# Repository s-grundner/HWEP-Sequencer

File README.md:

# HWEP - Sequencer [DE]

|           Neueste Renderung der Platine         |            Assemblierter Prototyp               |
|:-----------------------------------------------:|:-----------------------------------------------:|
|||

## Projektstatus

MIDI Erweiterung in Arbeit. CAD dateien e.g. Gehäuse sind noch nicht im Projekt inkludiert.
Um die Diagramme in der Dokumentation gut erkennen zu können, empfiehlt sich, das Dark-Mode-Theme von GitHub zu Verwenden.

## Repository Struktur

 - [**Hardware DOCS**](manufacturing/hwep_sequencer_v2)
 - [**Software DOCS**](src/SRC_HWEP_Sequencer_V2)

## KUB - Kurzbeschreibung

Der Sequenzer ist ein musisches Instrument, welches vom Benutzer einstellbare Töne nacheinander abspielt und dadurch eine Melodie erzeugt. Die Tonlage wird durch Potentiometer analog eingestellt und anschließend an die chromatische Skala angepasst. Die acht Töne werden mit jeder steigenden Flanke des Takts durchgeschaltet.

Mit einem Pause-Taster kann der Zyklus pausiert werden. Mit dem Reset-Taster kann zum Anfang des Zyklus gesprungen werden. Der "Show Key" Taster zeigt bei Betätigung die Gespielten Noten am Display an. Der Sequencer ist mit zwei Prescalern für Gate-Länge und Taktrate ausgestattet. Dieser teilt den Takt oder das Gate des Tones durch 1, 2, 4, 8 oder 16. Außerdem verfügt der Sequencer über eine Umschalttaste (Shift), die das Funktionsspektrum erweitern. Die Dokumentation für die Taster befindet sich in der Funktionsbeschreibung.

Zum Bedienen des Sequencers gibt es verschiedene Parameter, die mithilfe eines Dreh-Encoders gesteuert werden können. Der Dreh-Encoder hat einen integrierten Taster, mit welchem man die Parameter, die man verändern will, einstellen kann. Die Veränderung der Parameter wird je nach Modus an verschiedenen Status LEDs und Anzeigen abgezeichnet.

Der Sequencer wird mit dem einem RTOS am ESP32 32-bit Microcontroller betrieben. Der Digitale Audioausgang erfolgt über das I²S (Inter-IC-Sound) Protokoll und kann 16-Bit Sounds bei einer Abtastrate von 44.1kHz übertragen und durch einen I²S-DAC (PCM5102a) direkt als Audio-Signal ausgegeben werden.

## FUB - Funktionsbeschreibung

#### 1. 8 Potentiometer als analoger Eingang

 - dient als analoger Eingang für die Tonlage der einzelnen Töne
 - jedes Potentiometer umfasst 24 Halbtöne bzw. zwei Oktaven
 - die analogen Werte einem 8 Channel ADC (ADC088S052) über die SPI Schnittstelle eingelesen

#### 2. 16 Status LED’s:

 - 8 EN-LED’s:
   - zeigen an, welcher Ton spielen wird oder stummgeschalten ist (LED aus)
 - 8 Index/Cursor-LED’s:
   - **Index:** zeigen an, welcher Ton gerade spielt
   - **Cursor:** dient zum Anzeigen eines Cursors

#### 3. 3x 7-Segent Display:

 - nützen zur Anzeige von Parametern
 - werden mit einem MCP23S08 via die SPI Schnittstelle seriell angesteuert
 
#### 4. Dreh-Encoder:

 - zum Einstellen der Parameter der verschiedenen Modi
 - um den Drehencoder befinden sich 12 RGB-LED’s, welche den Rotationstatus anzeigen
 
#### 5. Taster: 

> Jeder Taster wird mittels eines MCP23S08 via SPI eingelesen.

 - **Pause:** pausiert den Zyklus
 - **Reset:** setzt den Zyklus asynchron zurück
 - **Show Keys:** zeigt die gespielten Noten am Display
 - **Shift:** zum Einstellen der Parameter der verschiedenen Modi
 - e. **Prescaler:** einstellen von zwei verschiedenen Prescalern für Gate und Takt
   - 5 Taster für jeden Prescaler
   - Tasten werden auf 4-Bit Priorität-Encodiert
 
#### 6. 4 Modi

> Jeder Modus verändert die Anzeigen an den Status LED’s und Displays bzw. die Funktionalität verschiedener Eingaben. Nach wechseln eines Modus wird der aktuelle Modus am 7-Segment Display angezeigt, bis die Anzeige benötigt wird, um einen Parameter anzuzeigen.
 
 - BPM:
   - **7-Segment Display:** zeigt die eingestellten BPM bzw. die Wellenform an
   - **Index/Cursor:** zeigt den Index an
   - **Drehencoder:** zum Verändern der BPM
   - **Shift Taster:** Drehencoder verändert die Wellenform
 - Tonleiter Einstellungen:
   - **7-Segment Display:** zeigt den Tonleiter bzw. den Modalen Tonleiter an.
   - **Index/Cursor:** zeigt den Index an
   - **Drehencoder:** zum Verändern den Tonleiter
   - **Shift Taster:** verändert den Modus des Tonleiters (Dur,Moll…)
 - Enable/Reset:
   - **7-Segment Display:**
   - **Index/Cursor:** zeigt den Cursor an
   - **Drehencoder:** bewegt den Cursor. Dort wo der Cursor stehen bleibt, setzt sich der Zyklus zurück.
   - **Shift Taster:** stummt/entstummt einen Ton an der Cursorstellung
 
 - Transpose:
   - **7-Segment Display:** zeigt an um wieviel Halbtöne die Melodie transponiert wird
   - **Index/Cursor:** zeigt den Index an
   - **Drehencoder:** Transponiert die Tonlage um einen Halbton
   - **Shift Taster:** Drehencoder verändert die Tonlage um eine Oktave
 
#### 7. ESP32 32-Bit Microcontroller:

 - Zentrale Recheneinheit für den Sequenzer
 - Berechnung der Wavetables
 - SPI als Übertragungsprotokoll zur Ansteuerung der internen Peripherien
 - Audio-Output:
   - Digitale Audioübertragung via I²S Protokoll
   - 16-bit Audio-Signale mit Abtastrate von 44,1kHz
   - Ein I²S-DAC (PCM5102a) decodiert die Audio-Daten und gibt sie Analog an eine 3,5mm Klinkenbuchse aus.
   - Kompatibel mit Trinity Endstufe

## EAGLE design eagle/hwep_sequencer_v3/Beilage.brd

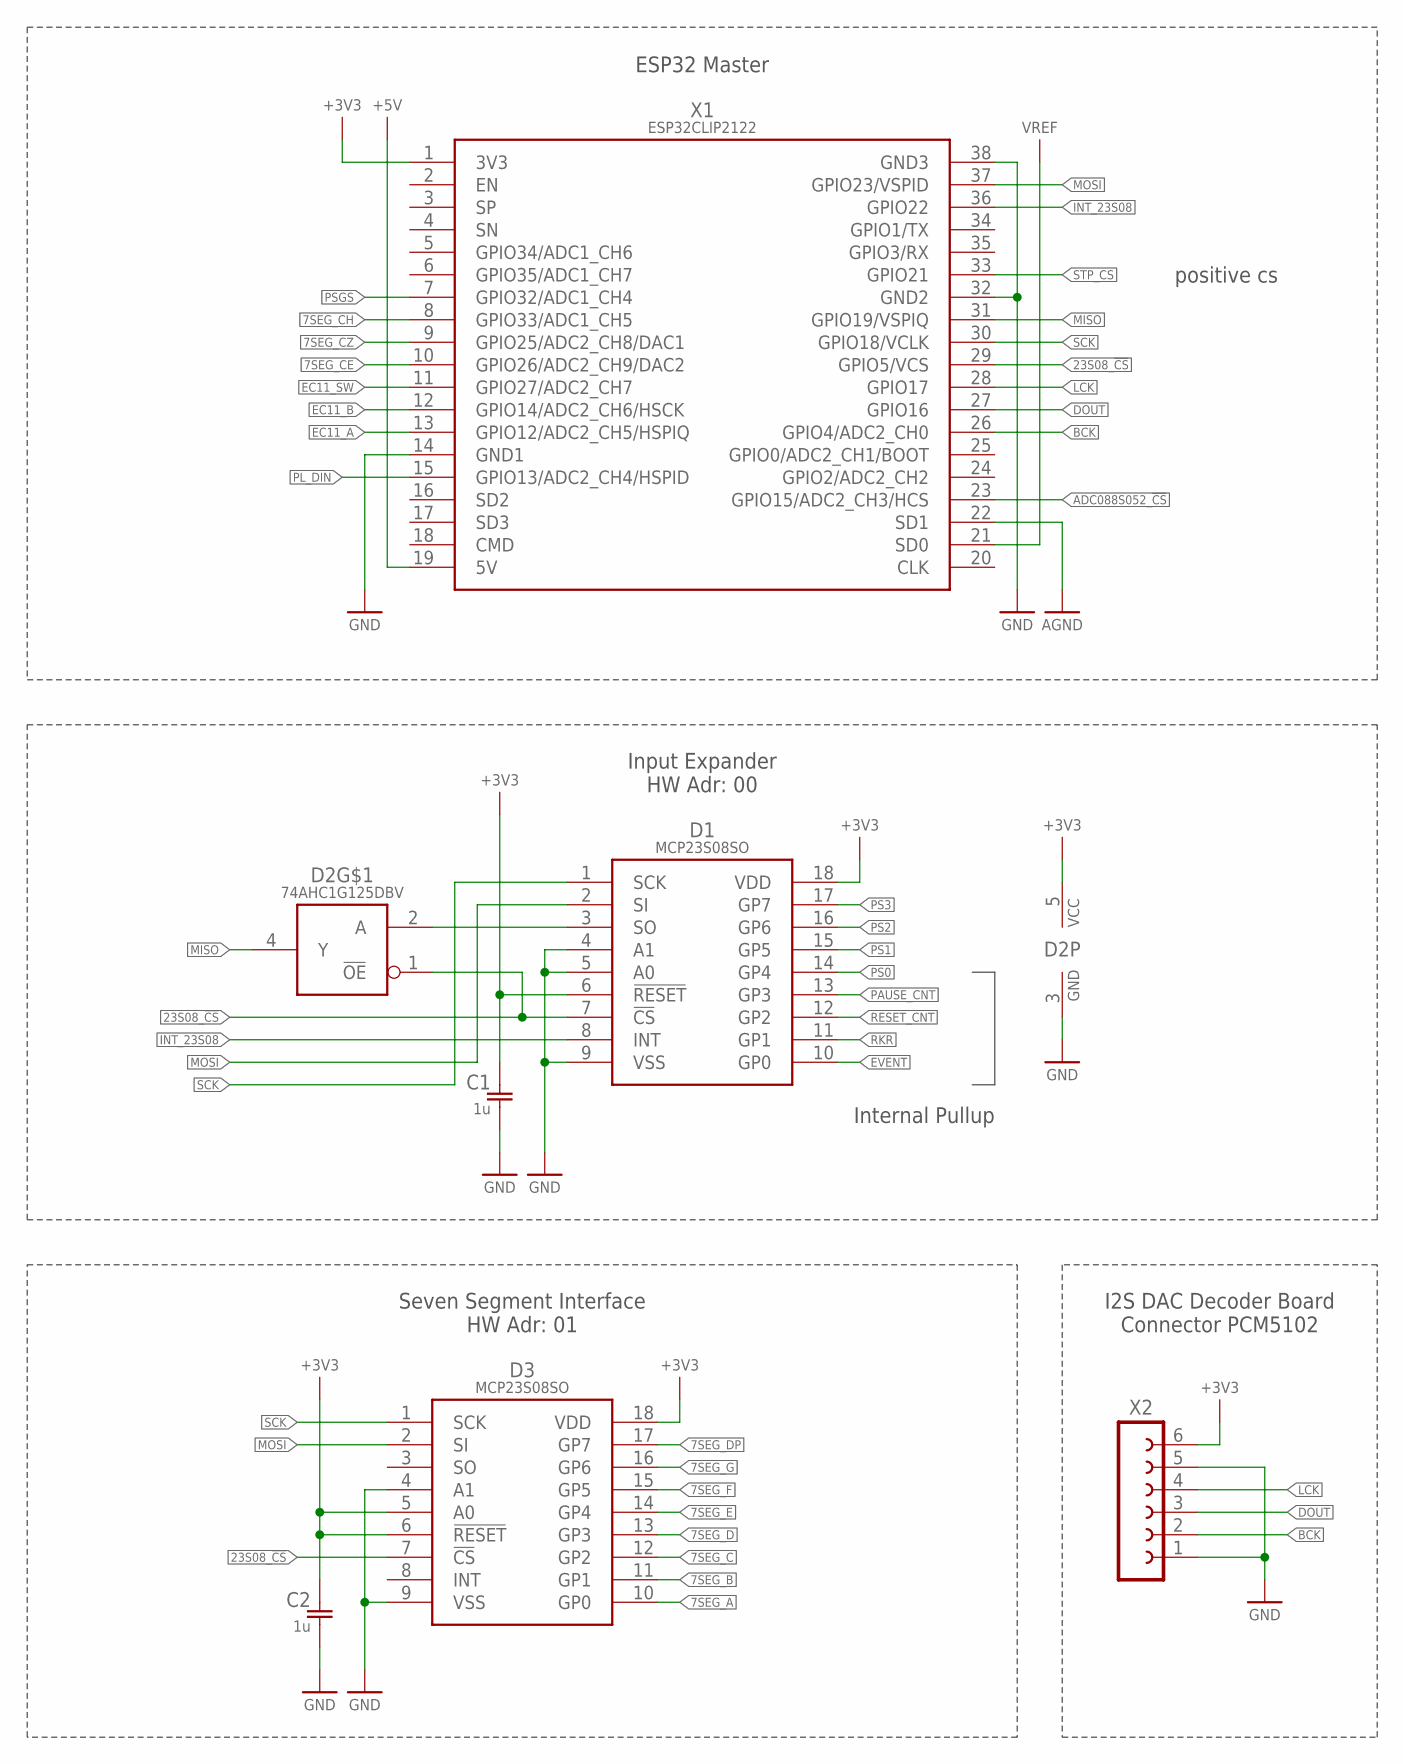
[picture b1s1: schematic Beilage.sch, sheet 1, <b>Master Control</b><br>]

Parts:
C1, C2: 1u; C0805
D1, D3: MCP23S08SO; SO18W
D2: 74AHC1G125DBV; SOT23-5
X1: ESP32CLIP2122; ESP32-DEVKIT-C-CLIP
X2: FE06-1; FE06

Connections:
7SEG_A: D3.10 (GP0); also elsewhere on the board
7SEG_B: D3.11 (GP1); also elsewhere on the board
7SEG_C: D3.12 (GP2); also elsewhere on the board
7SEG_CE: X1.10 (GPIO26/ADC2_CH9/DAC2); also elsewhere on the board
7SEG_CH: X1.8 (GPIO33/ADC1_CH5); also elsewhere on the board
7SEG_CZ: X1.9 (GPIO25/ADC2_CH8/DAC1); also elsewhere on the board
7SEG_D: D3.13 (GP3); also elsewhere on the board
7SEG_DP: D3.17 (GP7); also elsewhere on the board
7SEG_E: D3.14 (GP4); also elsewhere on the board
7SEG_F: D3.15 (GP5); also elsewhere on the board
7SEG_G: D3.16 (GP6); also elsewhere on the board
23S08_!CS: D1.7 (!CS), D2.1 (!OE), D3.7 (!CS), X1.29 (GPIO5/VCS)
+3V3: C1.1, C2.1, D1.6 (!RESET), D1.18 (VDD), D2.5 (VCC), D3.5 (A0), D3.6 (!RESET), D3.18 (VDD), X1.1 (3V3), X2.6; also elsewhere on the board
+5V: X1.19 (5V); also elsewhere on the board
ADC088S052_!CS: X1.23 (GPIO15/ADC2_CH3/HCS); also elsewhere on the board
AGND: X1.22 (SD1); also elsewhere on the board
BCK: X1.26 (GPIO4/ADC2_CH0), X2.2
DOUT: X1.27 (GPIO16), X2.3
EC11_A: X1.13 (GPIO12/ADC2_CH5/HSPIQ); also elsewhere on the board
EC11_B: X1.12 (GPIO14/ADC2_CH6/HSCK); also elsewhere on the board
EC11_SW: X1.11 (GPIO27/ADC2_CH7); also elsewhere on the board
EVENT: D1.10 (GP0); also elsewhere on the board
GND: C1.2, C2.2, D1.4 (A1), D1.5 (A0), D1.9 (VSS), D2.3 (GND), D3.4 (A1), D3.9 (VSS), X1.14 (GND1), X1.32 (GND2), X1.38 (GND3), X2.1, X2.5; also elsewhere on the board
INT_23S08: D1.8 (INT), X1.36 (GPIO22)
LCK: X1.28 (GPIO17), X2.4
MISO: D2.4 (Y), X1.31 (GPIO19/VSPIQ); also elsewhere on the board
MOSI: D1.2 (SI), D3.2 (SI), X1.37 (GPIO23/VSPID); also elsewhere on the board
unnamed: D1.3 (SO), D2.2 (A)
PAUSE_CNT: D1.13 (GP3); also elsewhere on the board
PL_DIN: X1.15 (GPIO13/ADC2_CH4/HSPID); also elsewhere on the board
PS0: D1.14 (GP4); also elsewhere on the board
PS1: D1.15 (GP5); also elsewhere on the board
PS2: D1.16 (GP6); also elsewhere on the board
PS3: D1.17 (GP7); also elsewhere on the board
PSGS: X1.7 (GPIO32/ADC1_CH4); also elsewhere on the board
RESET_CNT: D1.12 (GP2); also elsewhere on the board
RKR: D1.11 (GP1); also elsewhere on the board
SCK: D1.1 (SCK), D3.1 (SCK), X1.30 (GPIO18/VCLK); also elsewhere on the board
STP_CS: X1.33 (GPIO21); also elsewhere on the board
VREF: X1.21 (SD0); also elsewhere on the board

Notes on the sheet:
Seven Segment Interface HW Adr: 01
ESP32 Master
I2S DAC Decoder Board Connector PCM5102
Input Expander HW Adr: 00
Internal Pullup
positive cs

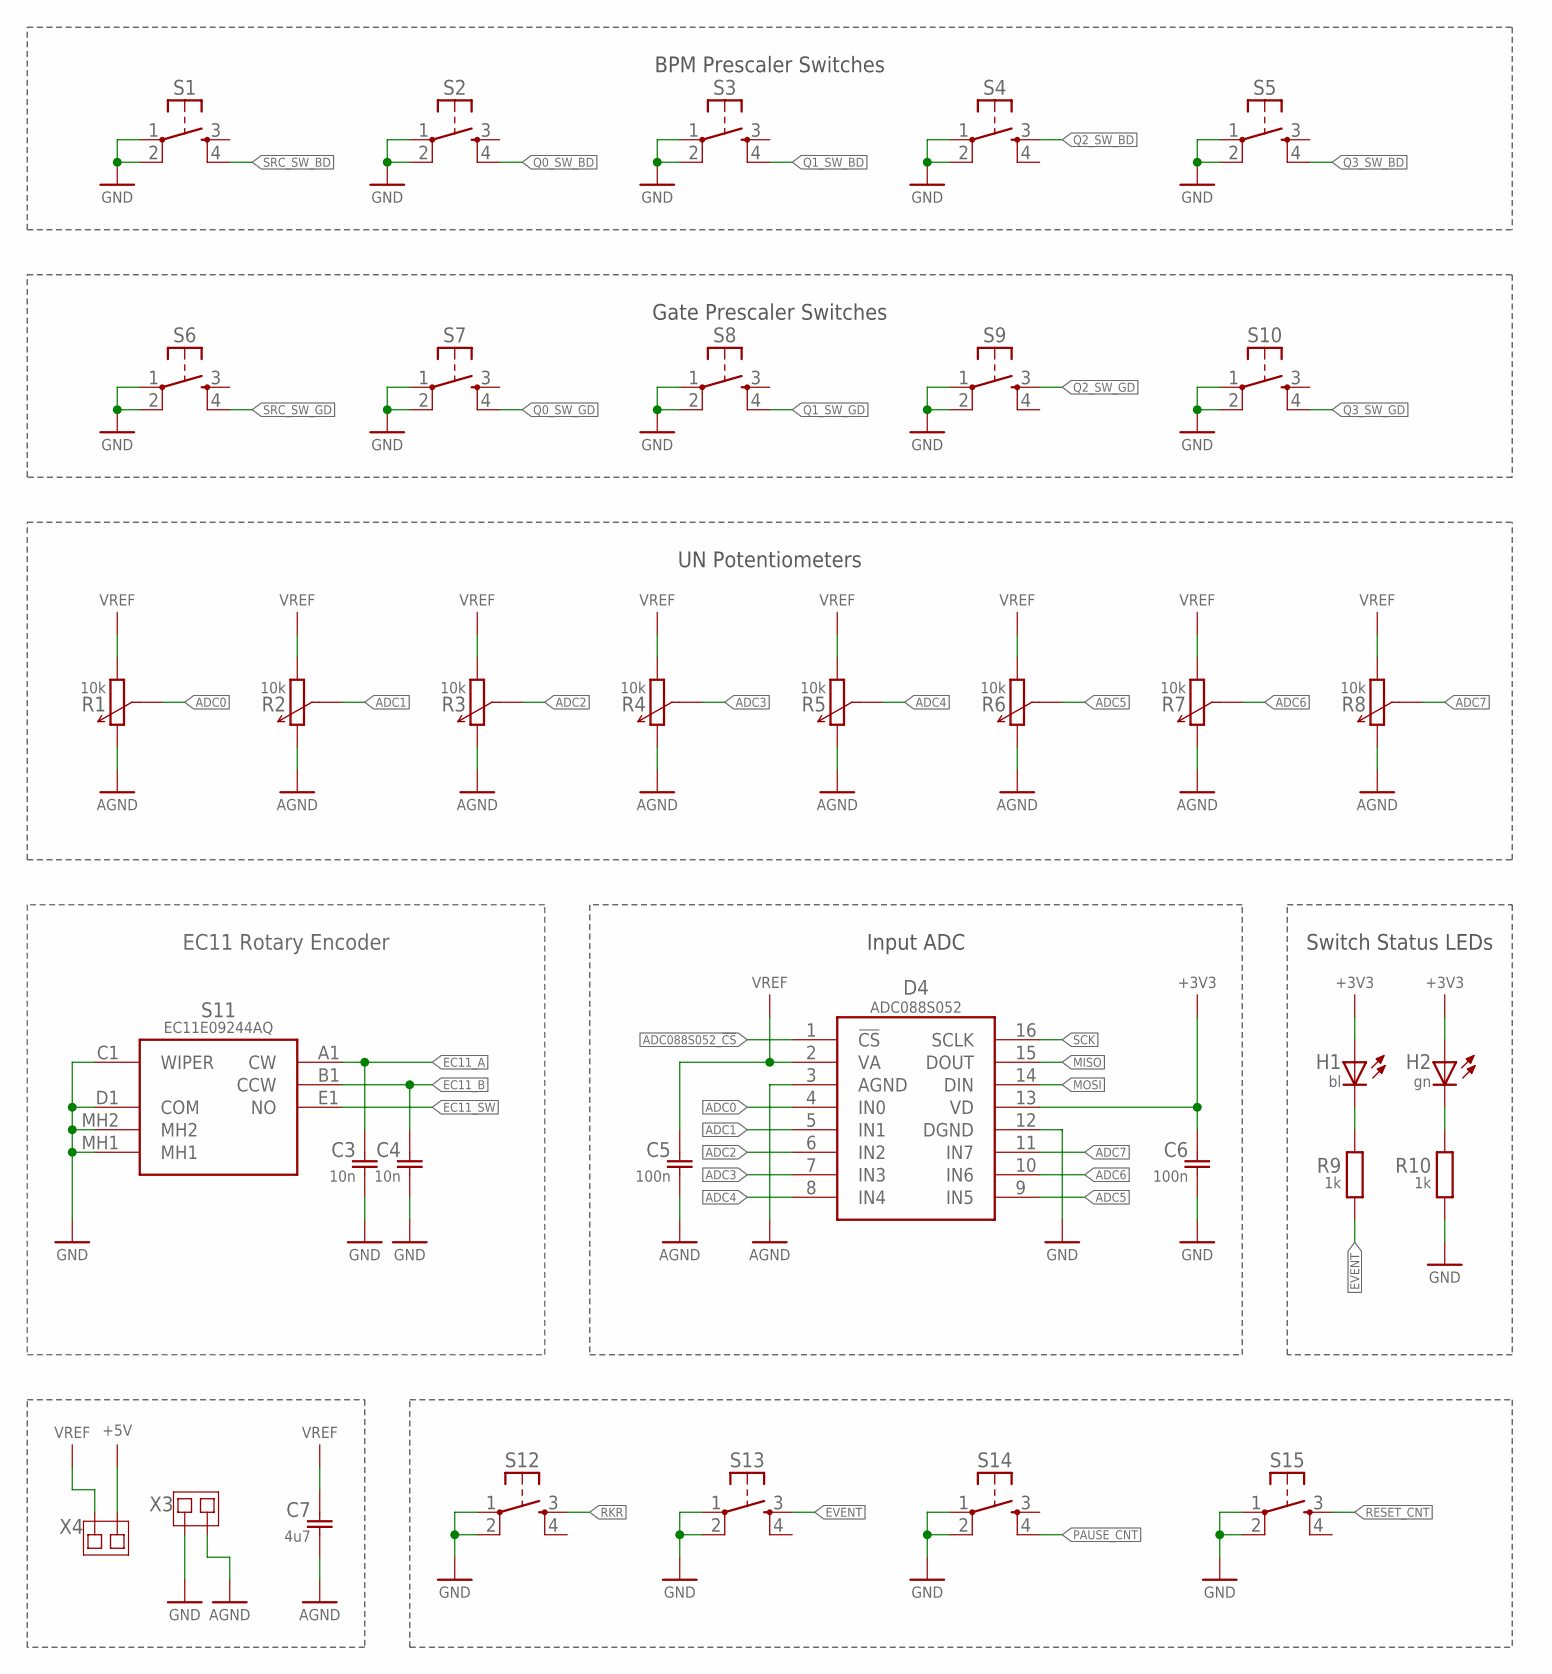
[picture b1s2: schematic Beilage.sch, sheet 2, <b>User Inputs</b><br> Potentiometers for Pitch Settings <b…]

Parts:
C3, C4: 10n; C0805
C5, C6: 100n; C0805
C7: 4u7; C0805
D4: ADC088S052; TSSOP16
H1: bl; CHIPLED_1206
H2: gn; CHIPLED_1206
R1, R2, R3, R4, R5, R6, R7, R8: 10k; P160LB
R9, R10: 1k; R0805
S1, S2, S3, S4, S5, S6, S7, S8, S9, S10, S12, S13, S14, S15: TASTE10XX; B3F-10XX
S11: EC11E09244AQ; EC11
X3, X4: JUMPSMD1FACH-1; MYLIB_SJ

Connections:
+3V3: C6.1, D4.13 (VD), H1.A, H2.A; also elsewhere on the board
+5V: X4.1; also elsewhere on the board
ADC0: D4.4 (IN0), R1.2 (3)
ADC1: D4.5 (IN1), R2.2 (3)
ADC2: D4.6 (IN2), R3.2 (3)
ADC3: D4.7 (IN3), R4.2 (3)
ADC4: D4.8 (IN4), R5.2 (3)
ADC5: D4.9 (IN5), R6.2 (3)
ADC6: D4.10 (IN6), R7.2 (3)
ADC7: D4.11 (IN7), R8.2 (3)
ADC088S052_!CS: D4.1 (!CS); also elsewhere on the board
AGND: C5.2, C7.2, D4.3 (AGND), R1.3 (2), R2.3 (2), R3.3 (2), R4.3 (2), R5.3 (2), R6.3 (2), R7.3 (2), R8.3 (2), X3.2; also elsewhere on the board
EC11_A: C3.1, S11.A1 (CW); also elsewhere on the board
EC11_B: C4.1, S11.B1 (CCW); also elsewhere on the board
EC11_SW: S11.E1 (NO); also elsewhere on the board
EVENT: R9.1, S13.3 (S); also elsewhere on the board
GND: C3.2, C4.2, C6.2, D4.12 (DGND), R10.1, S1.1, S1.2 (P1), S2.1, S2.2 (P1), S3.1, S3.2 (P1), S4.1, S4.2 (P1), S5.1, S5.2 (P1), S6.1, S6.2 (P1), S7.1, S7.2 (P1), S8.1, S8.2 (P1), S9.1, S9.2 (P1), S10.1, S10.2 (P1), S11.C1 (WIPER), S11.D1 (COM), S11.MH1, S11.MH2, S12.1, S12.2 (P1), S13.1, S13.2 (P1), S14.1, S14.2 (P1), S15.1, S15.2 (P1), X3.1; also elsewhere on the board
MISO: D4.15 (DOUT); also elsewhere on the board
MOSI: D4.14 (DIN); also elsewhere on the board
unnamed: H2.C, R10.2
unnamed: H1.C, R9.2
PAUSE_CNT: S14.4 (S1); also elsewhere on the board
Q0_SW_BD: S2.4 (S1); also elsewhere on the board
Q0_SW_GD: S7.4 (S1); also elsewhere on the board
Q1_SW_BD: S3.4 (S1); also elsewhere on the board
Q1_SW_GD: S8.4 (S1); also elsewhere on the board
Q2_SW_BD: S4.3 (S); also elsewhere on the board
Q2_SW_GD: S9.3 (S); also elsewhere on the board
Q3_SW_BD: S5.4 (S1); also elsewhere on the board
Q3_SW_GD: S10.4 (S1); also elsewhere on the board
RESET_CNT: S15.3 (S); also elsewhere on the board
RKR: S12.3 (S); also elsewhere on the board
SCK: D4.16 (SCLK); also elsewhere on the board
SRC_SW_BD: S1.4 (S1); also elsewhere on the board
SRC_SW_GD: S6.4 (S1); also elsewhere on the board
VREF: C5.1, C7.1, D4.2 (VA), R1.1, R2.1, R3.1, R4.1, R5.1, R6.1, R7.1, R8.1, X4.2; also elsewhere on the board

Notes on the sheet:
UN Potentiometers
EC11 Rotary Encoder
BPM Prescaler Switches
Gate Prescaler Switches
Switch Status LEDs
Input ADC

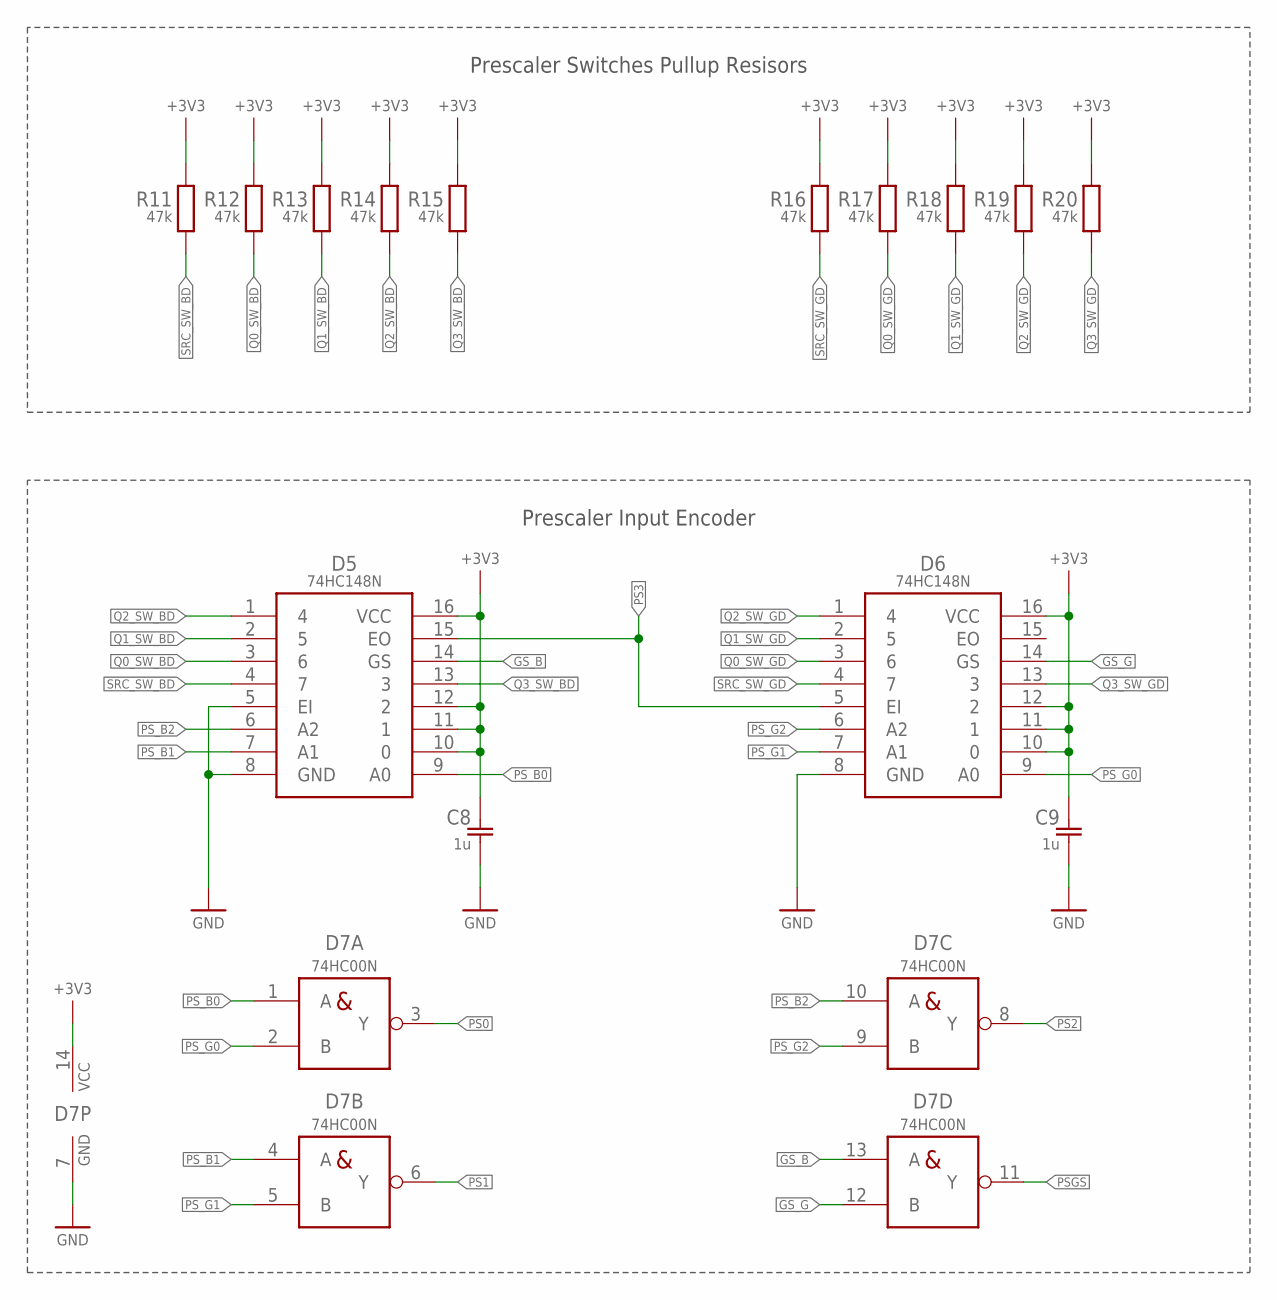
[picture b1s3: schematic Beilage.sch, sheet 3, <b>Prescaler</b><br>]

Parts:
C8, C9: 1u; C0805
D5, D6: 74HC148N; DIP16
D7: 74HC00N; DIP14
R11, R12, R13, R14, R15, R16, R17, R18, R19, R20: 47k; R0805

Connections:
+3V3: C8.1, C9.1, D5.10 (0), D5.11 (1), D5.12 (2), D5.16 (VCC), D6.10 (0), D6.11 (1), D6.12 (2), D6.16 (VCC), D7.14 (VCC), R11.2, R12.2, R13.2, R14.2, R15.2, R16.2, R17.2, R18.2, R19.2, R20.2; also elsewhere on the board
GND: C8.2, C9.2, D5.5 (EI), D5.8 (GND), D6.8 (GND), D7.7 (GND); also elsewhere on the board
GS_B: D5.14 (GS), D7.13 (A)
GS_G: D6.14 (GS), D7.12 (B)
PS0: D7.3 (Y); also elsewhere on the board
PS1: D7.6 (Y); also elsewhere on the board
PS2: D7.8 (Y); also elsewhere on the board
PS3: D5.15 (EO), D6.5 (EI); also elsewhere on the board
PSGS: D7.11 (Y); also elsewhere on the board
PS_B0: D5.9 (A0), D7.1 (A)
PS_B1: D5.7 (A1), D7.4 (A)
PS_B2: D5.6 (A2), D7.10 (A)
PS_G0: D6.9 (A0), D7.2 (B)
PS_G1: D6.7 (A1), D7.5 (B)
PS_G2: D6.6 (A2), D7.9 (B)
Q0_SW_BD: D5.3 (6), R12.1; also elsewhere on the board
Q0_SW_GD: D6.3 (6), R17.1; also elsewhere on the board
Q1_SW_BD: D5.2 (5), R13.1; also elsewhere on the board
Q1_SW_GD: D6.2 (5), R18.1; also elsewhere on the board
Q2_SW_BD: D5.1 (4), R14.1; also elsewhere on the board
Q2_SW_GD: D6.1 (4), R19.1; also elsewhere on the board
Q3_SW_BD: D5.13 (3), R15.1; also elsewhere on the board
Q3_SW_GD: D6.13 (3), R20.1; also elsewhere on the board
SRC_SW_BD: D5.4 (7), R11.1; also elsewhere on the board
SRC_SW_GD: D6.4 (7), R16.1; also elsewhere on the board

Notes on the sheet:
Prescaler Input Encoder
Prescaler Switches Pullup Resisors

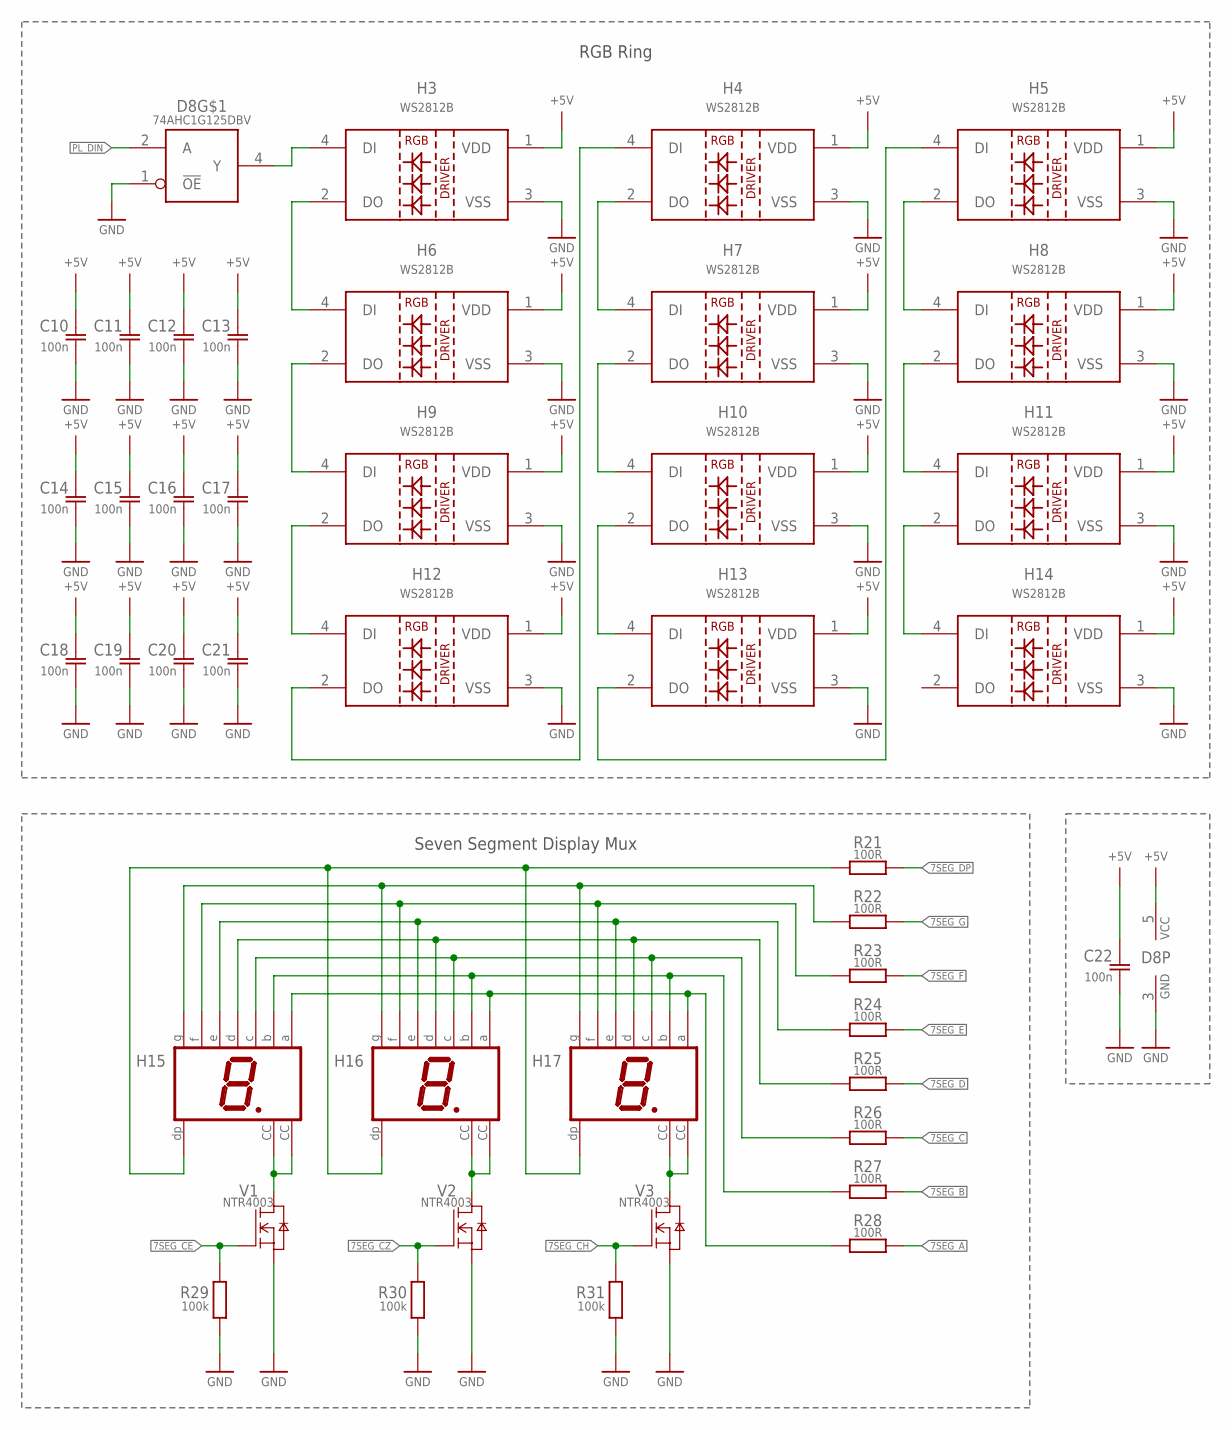
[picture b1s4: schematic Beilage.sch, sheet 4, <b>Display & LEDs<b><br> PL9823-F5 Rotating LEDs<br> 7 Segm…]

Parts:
C10, C11, C12, C13, C14, C15, C16, C17, C18, C19, C20, C21, C22: 100n; C0805
D8: 74AHC1G125DBV; SOT23-5
H3, H4, H5, H6, H7, H8, H9, H10, H11, H12, H13, H14: WS2812B
H15, H16, H17: HD-H103; HDSP-E
R21, R22, R23, R24, R25, R26, R27, R28: 100R; R0805
R29, R30, R31: 100k; R0805
V1, V2, V3: NTR4003; SOT23

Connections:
7SEG_A: R28.2; also elsewhere on the board
7SEG_B: R27.2; also elsewhere on the board
7SEG_C: R26.2; also elsewhere on the board
7SEG_CE: R29.2, V1.1 (G); also elsewhere on the board
7SEG_CH: R31.2, V3.1 (G); also elsewhere on the board
7SEG_CZ: R30.2, V2.1 (G); also elsewhere on the board
7SEG_D: R25.2; also elsewhere on the board
7SEG_DP: R21.2; also elsewhere on the board
7SEG_E: R24.2; also elsewhere on the board
7SEG_F: R23.2; also elsewhere on the board
7SEG_G: R22.2; also elsewhere on the board
+5V: C10.1, C11.1, C12.1, C13.1, C14.1, C15.1, C16.1, C17.1, C18.1, C19.1, C20.1, C21.1, C22.1, D8.5 (VCC), H3.1 (VDD), H4.1 (VDD), H5.1 (VDD), H6.1 (VDD), H7.1 (VDD), H8.1 (VDD), H9.1 (VDD), H10.1 (VDD), H11.1 (VDD), H12.1 (VDD), H13.1 (VDD), H14.1 (VDD); also elsewhere on the board
GND: C10.2, C11.2, C12.2, C13.2, C14.2, C15.2, C16.2, C17.2, C18.2, C19.2, C20.2, C21.2, C22.2, D8.1 (!OE), D8.3 (GND), H3.3 (VSS), H4.3 (VSS), H5.3 (VSS), H6.3 (VSS), H7.3 (VSS), H8.3 (VSS), H9.3 (VSS), H10.3 (VSS), H11.3 (VSS), H12.3 (VSS), H13.3 (VSS), H14.3 (VSS), R29.1, R30.1, R31.1, V1.2 (S), V2.2 (S), V3.2 (S); also elsewhere on the board
unnamed: D8.4 (Y), H3.4 (DI)
unnamed: H6.2 (DO), H9.4 (DI)
unnamed: H3.2 (DO), H6.4 (DI)
unnamed: H8.2 (DO), H11.4 (DI)
unnamed: H15.DP, H16.DP, H17.DP, R21.1
unnamed: H15.G, H16.G, H17.G, R22.1
unnamed: H15.F, H16.F, H17.F, R23.1
unnamed: H15.A, H16.A, H17.A, R28.1
unnamed: H15.B, H16.B, H17.B, R27.1
unnamed: H15.CC1 (CC), H15.CC2 (CC), V1.3 (D)
unnamed: H15.D, H16.D, H17.D, R25.1
unnamed: H10.2 (DO), H13.4 (DI)
unnamed: H5.4 (DI), H13.2 (DO)
unnamed: H5.2 (DO), H8.4 (DI)
unnamed: H16.CC1 (CC), H16.CC2 (CC), V2.3 (D)
unnamed: H17.CC1 (CC), H17.CC2 (CC), V3.3 (D)
unnamed: H7.2 (DO), H10.4 (DI)
unnamed: H9.2 (DO), H12.4 (DI)
unnamed: H11.2 (DO), H14.4 (DI)
unnamed: H4.4 (DI), H12.2 (DO)
unnamed: H4.2 (DO), H7.4 (DI)
unnamed: H15.C, H16.C, H17.C, R26.1
unnamed: H15.E, H16.E, H17.E, R24.1
PL_DIN: D8.2 (A); also elsewhere on the board

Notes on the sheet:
Seven Segment Display Mux
RGB Ring

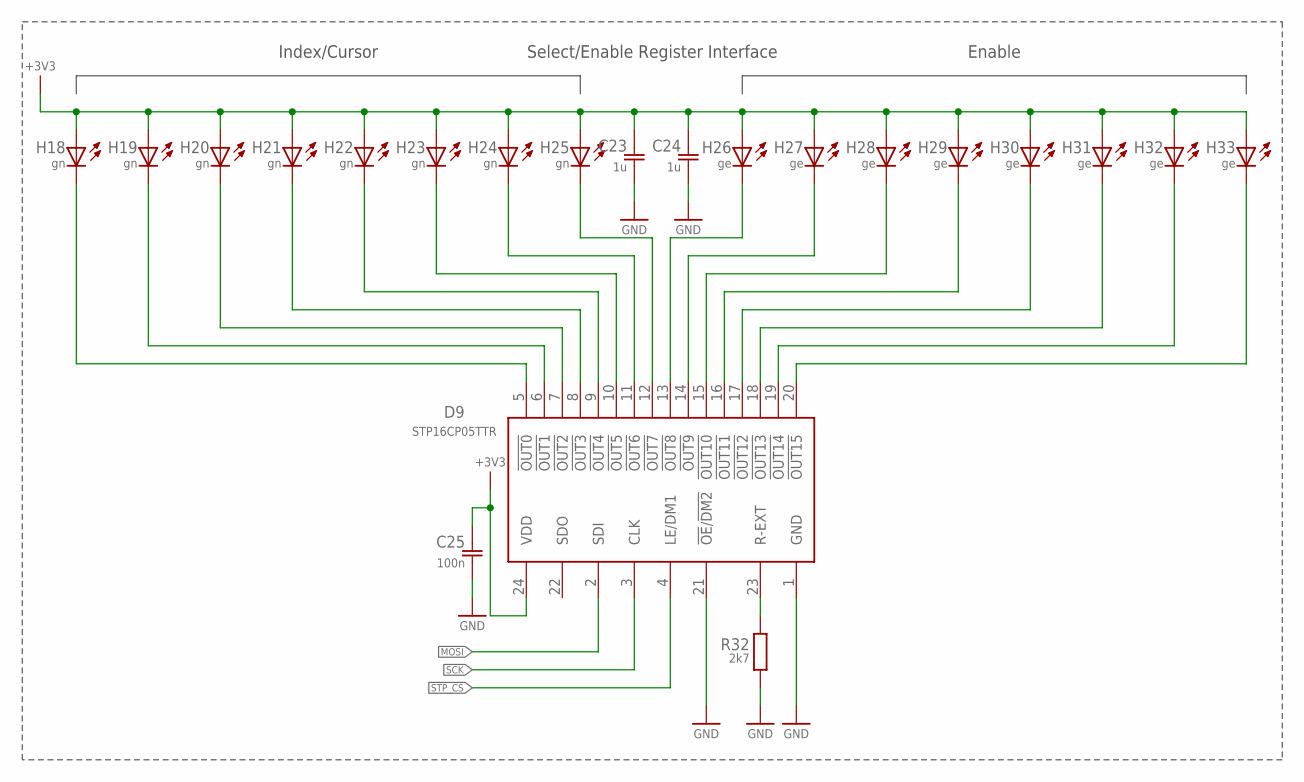
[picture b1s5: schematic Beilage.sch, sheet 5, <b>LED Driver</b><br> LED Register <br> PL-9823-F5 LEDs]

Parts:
C23, C24: 1u; C0805
C25: 100n; C0805
D9: STP16CP05TTR; TSSOP24
H18, H19, H20, H21, H22, H23, H24, H25: gn; LED5MM
H26, H27, H28, H29, H30, H31, H32, H33: ge; LED5MM
R32: 2k7; R0805

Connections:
+3V3: C23.1, C24.1, C25.1, D9.24 (VDD), H18.A, H19.A, H20.A, H21.A, H22.A, H23.A, H24.A, H25.A, H26.A, H27.A, H28.A, H29.A, H30.A, H31.A, H32.A, H33.A; also elsewhere on the board
GND: C23.2, C24.2, C25.2, D9.1 (GND), D9.21 (!OE!/!DM2), R32.1; also elsewhere on the board
MOSI: D9.2 (SDI); also elsewhere on the board
unnamed: D9.5 (!OUT0), H18.K (C)
unnamed: D9.6 (!OUT1), H19.K (C)
unnamed: D9.7 (!OUT2), H20.K (C)
unnamed: D9.8 (!OUT3), H21.K (C)
unnamed: D9.9 (!OUT4), H22.K (C)
unnamed: D9.10 (!OUT5), H23.K (C)
unnamed: D9.11 (!OUT6), H24.K (C)
unnamed: D9.12 (!OUT7), H25.K (C)
unnamed: D9.13 (!OUT8), H26.K (C)
unnamed: D9.14 (!OUT9), H27.K (C)
unnamed: D9.15 (!OUT10), H28.K (C)
unnamed: D9.16 (!OUT11), H29.K (C)
unnamed: D9.17 (!OUT12), H30.K (C)
unnamed: D9.18 (!OUT13), H31.K (C)
unnamed: D9.19 (!OUT14), H32.K (C)
unnamed: D9.20 (!OUT15), H33.K (C)
unnamed: D9.23 (R-EXT), R32.2
SCK: D9.3 (CLK); also elsewhere on the board
STP_CS: D9.4 (LE/DM1); also elsewhere on the board

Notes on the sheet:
Index/Cursor
Enable
Select/Enable Register Interface

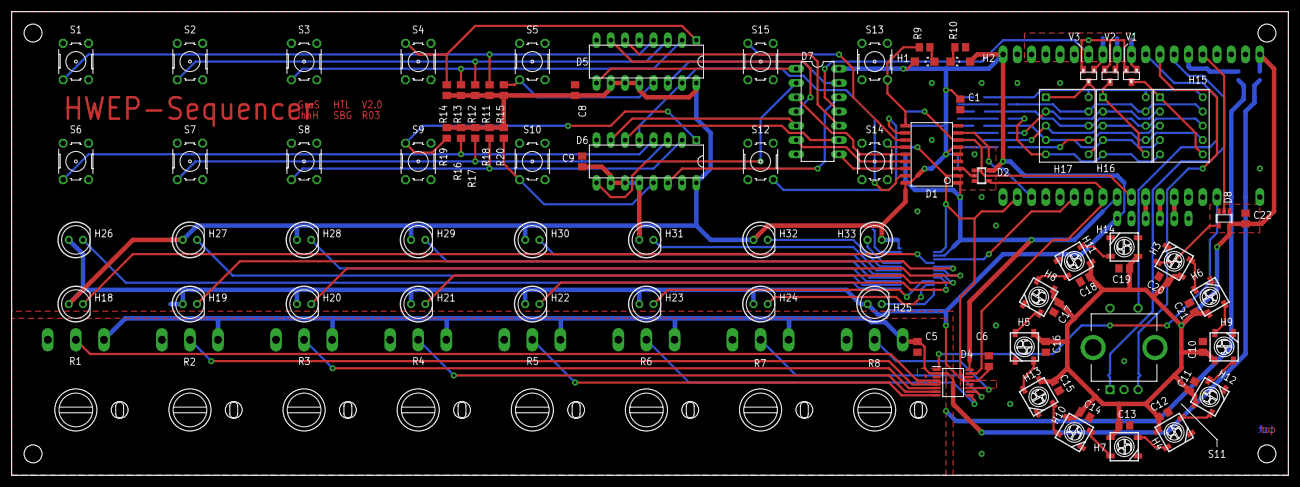
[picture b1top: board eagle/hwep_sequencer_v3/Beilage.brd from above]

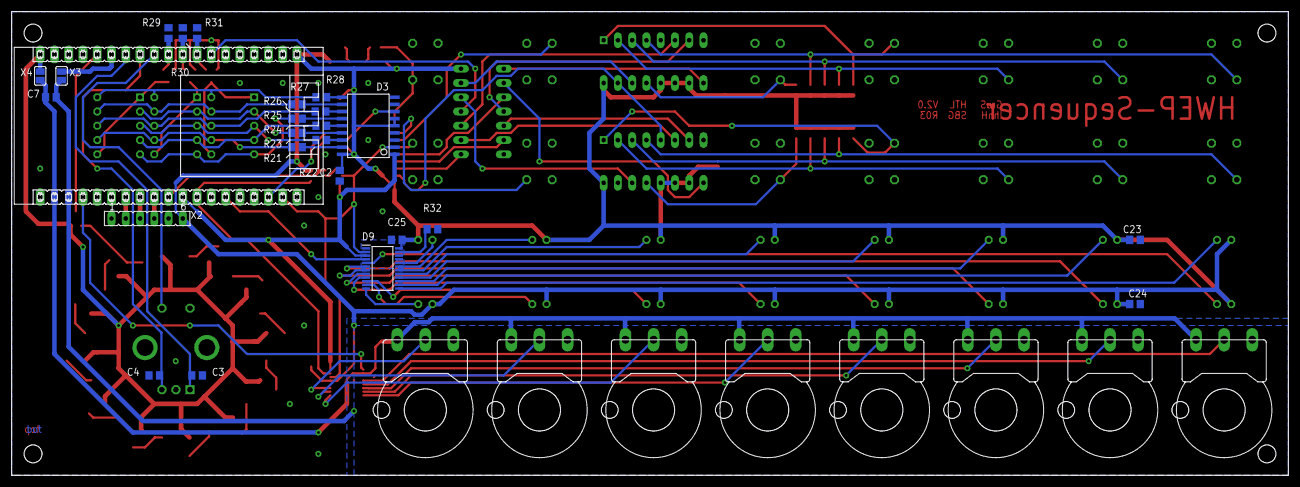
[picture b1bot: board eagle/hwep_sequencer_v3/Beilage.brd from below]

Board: 2 copper layers, 227.3 x 82.5 mm, 123 parts (25 on the bottom side), 108 nets.

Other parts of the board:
FABRICATION: FABRIACTION
MEASURE: MEASURE
